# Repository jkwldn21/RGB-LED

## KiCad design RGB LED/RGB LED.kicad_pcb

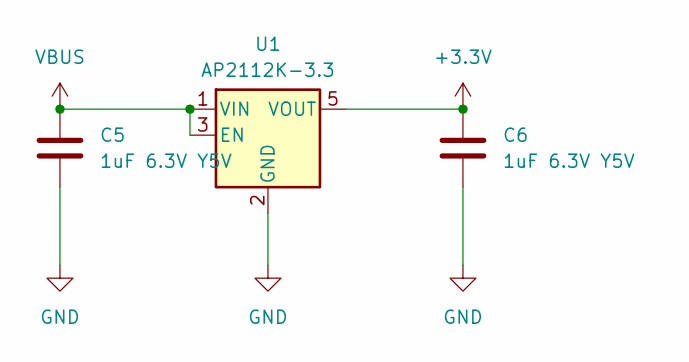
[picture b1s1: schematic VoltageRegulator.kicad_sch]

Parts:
C5, C6: 1uF 6.3V Y5V; C_0603_1608Metric
U1: AP2112K-3.3; SOT-23-5

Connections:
+3.3V: C6.1, U1.5 (VOUT); also elsewhere on the board
GND: C5.2, C6.2, U1.2 (GND); also elsewhere on the board
VBUS: C5.1, U1.1 (VIN), U1.3 (EN); also elsewhere on the board

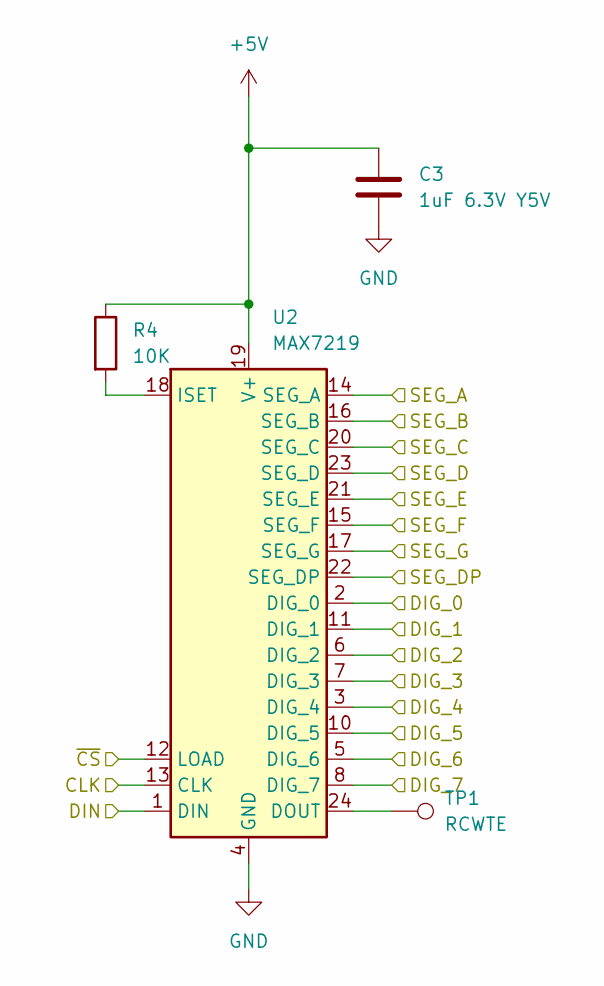
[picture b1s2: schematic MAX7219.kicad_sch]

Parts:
C3: 1uF 6.3V Y5V; C_0603_1608Metric
R4: 10K; R_0603_1608Metric
TP1: RCWTE; TestPoint_Keystone_5015_Micro-Minature
U2: MAX7219; SOP-24_7.5x15.4mm_P1.27mm

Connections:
+5V: C3.1, R4.1, U2.19 (V+)
/CLK: U2.13 (CLK); also elsewhere on the board
/DIN: U2.1 (DIN); also elsewhere on the board
/LED_Matrix/DIG_0: U2.2 (DIG_0); also elsewhere on the board
/LED_Matrix/DIG_1: U2.11 (DIG_1); also elsewhere on the board
/LED_Matrix/DIG_2: U2.6 (DIG_2); also elsewhere on the board
/LED_Matrix/DIG_3: U2.7 (DIG_3); also elsewhere on the board
/LED_Matrix/DIG_4: U2.3 (DIG_4); also elsewhere on the board
/LED_Matrix/DIG_5: U2.10 (DIG_5); also elsewhere on the board
/LED_Matrix/DIG_6: U2.5 (DIG_6); also elsewhere on the board
/LED_Matrix/DIG_7: U2.8 (DIG_7); also elsewhere on the board
/LED_Matrix/SEG_A: U2.14 (SEG_A); also elsewhere on the board
/LED_Matrix/SEG_B: U2.16 (SEG_B); also elsewhere on the board
/LED_Matrix/SEG_C: U2.20 (SEG_C); also elsewhere on the board
/LED_Matrix/SEG_D: U2.23 (SEG_D); also elsewhere on the board
/LED_Matrix/SEG_DP: U2.22 (SEG_DP); also elsewhere on the board
/LED_Matrix/SEG_E: U2.21 (SEG_E); also elsewhere on the board
/LED_Matrix/SEG_F: U2.15 (SEG_F); also elsewhere on the board
/LED_Matrix/SEG_G: U2.17 (SEG_G); also elsewhere on the board
/~CS: U2.12 (LOAD); also elsewhere on the board
GND: C3.2, U2.4 (GND), U2.9 (GND); also elsewhere on the board
unnamed: TP1.1, U2.24 (DOUT)
unnamed: R4.2, U2.18 (ISET)

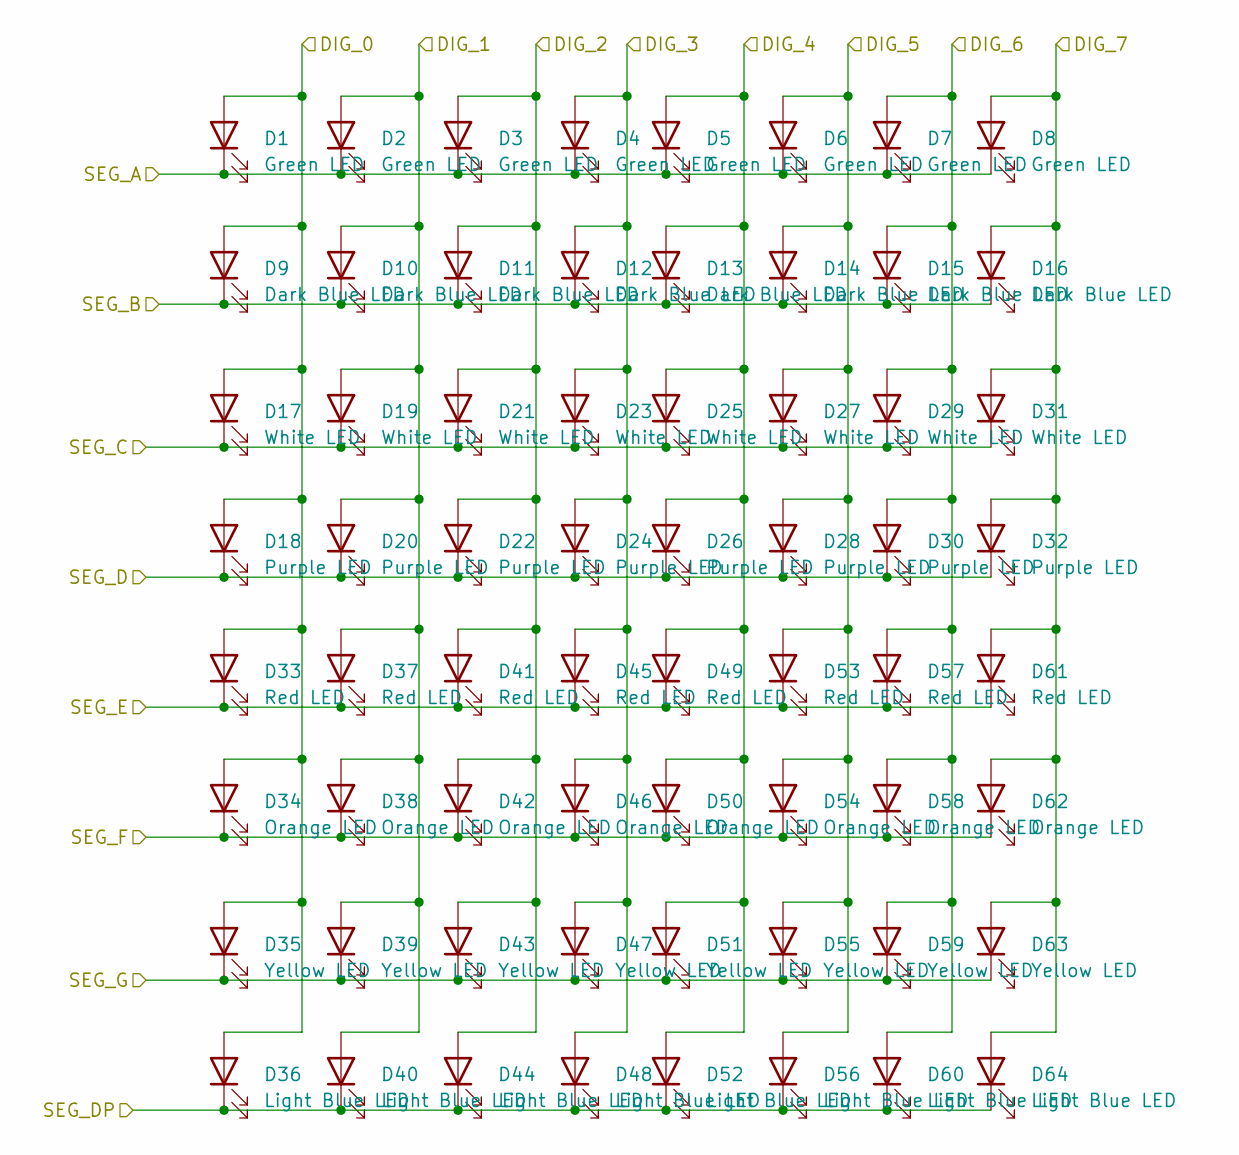
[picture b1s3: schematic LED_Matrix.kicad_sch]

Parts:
D1, D2, D3, D4, D5, D6, D7, D8: Green LED; LED_0603_1608Metric
D9, D10, D11, D12, D13, D14, D15, D16: Dark Blue LED; LED_0603_1608Metric
D17, D19, D21, D23, D25, D27, D29, D31: White LED; LED_0603_1608Metric
D18, D20, D22, D24, D26, D28, D30, D32: Purple LED; LED_0603_1608Metric
D33, D37, D41, D45, D49, D53, D57, D61: Red LED; LED_0603_1608Metric
D34, D38, D42, D46, D50, D54, D58, D62: Orange LED; LED_0603_1608Metric
D35, D39, D43, D47, D51, D55, D59, D63: Yellow LED; LED_0603_1608Metric
D36, D40, D44, D48, D52, D56, D60, D64: Light Blue LED; LED_0603_1608Metric

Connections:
/LED_Matrix/DIG_0: D1.2 (A), D9.2 (A), D17.2 (A), D18.2 (A), D33.2 (A), D34.2 (A), D35.2 (A), D36.2 (A); also elsewhere on the board
/LED_Matrix/DIG_1: D2.2 (A), D10.2 (A), D19.2 (A), D20.2 (A), D37.2 (A), D38.2 (A), D39.2 (A), D40.2 (A); also elsewhere on the board
/LED_Matrix/DIG_2: D3.2 (A), D11.2 (A), D21.2 (A), D22.2 (A), D41.2 (A), D42.2 (A), D43.2 (A), D44.2 (A); also elsewhere on the board
/LED_Matrix/DIG_3: D4.2 (A), D12.2 (A), D23.2 (A), D24.2 (A), D45.2 (A), D46.2 (A), D47.2 (A), D48.2 (A); also elsewhere on the board
/LED_Matrix/DIG_4: D5.2 (A), D13.2 (A), D25.2 (A), D26.2 (A), D49.2 (A), D50.2 (A), D51.2 (A), D52.2 (A); also elsewhere on the board
/LED_Matrix/DIG_5: D6.2 (A), D14.2 (A), D27.2 (A), D28.2 (A), D53.2 (A), D54.2 (A), D55.2 (A), D56.2 (A); also elsewhere on the board
/LED_Matrix/DIG_6: D7.2 (A), D15.2 (A), D29.2 (A), D30.2 (A), D57.2 (A), D58.2 (A), D59.2 (A), D60.2 (A); also elsewhere on the board
/LED_Matrix/DIG_7: D8.2 (A), D16.2 (A), D31.2 (A), D32.2 (A), D61.2 (A), D62.2 (A), D63.2 (A), D64.2 (A); also elsewhere on the board
/LED_Matrix/SEG_A: D1.1 (K), D2.1 (K), D3.1 (K), D4.1 (K), D5.1 (K), D6.1 (K), D7.1 (K), D8.1 (K); also elsewhere on the board
/LED_Matrix/SEG_B: D9.1 (K), D10.1 (K), D11.1 (K), D12.1 (K), D13.1 (K), D14.1 (K), D15.1 (K), D16.1 (K); also elsewhere on the board
/LED_Matrix/SEG_C: D17.1 (K), D19.1 (K), D21.1 (K), D23.1 (K), D25.1 (K), D27.1 (K), D29.1 (K), D31.1 (K); also elsewhere on the board
/LED_Matrix/SEG_D: D18.1 (K), D20.1 (K), D22.1 (K), D24.1 (K), D26.1 (K), D28.1 (K), D30.1 (K), D32.1 (K); also elsewhere on the board
/LED_Matrix/SEG_DP: D36.1 (K), D40.1 (K), D44.1 (K), D48.1 (K), D52.1 (K), D56.1 (K), D60.1 (K), D64.1 (K); also elsewhere on the board
/LED_Matrix/SEG_E: D33.1 (K), D37.1 (K), D41.1 (K), D45.1 (K), D49.1 (K), D53.1 (K), D57.1 (K), D61.1 (K); also elsewhere on the board
/LED_Matrix/SEG_F: D34.1 (K), D38.1 (K), D42.1 (K), D46.1 (K), D50.1 (K), D54.1 (K), D58.1 (K), D62.1 (K); also elsewhere on the board
/LED_Matrix/SEG_G: D35.1 (K), D39.1 (K), D43.1 (K), D47.1 (K), D51.1 (K), D55.1 (K), D59.1 (K), D63.1 (K); also elsewhere on the board

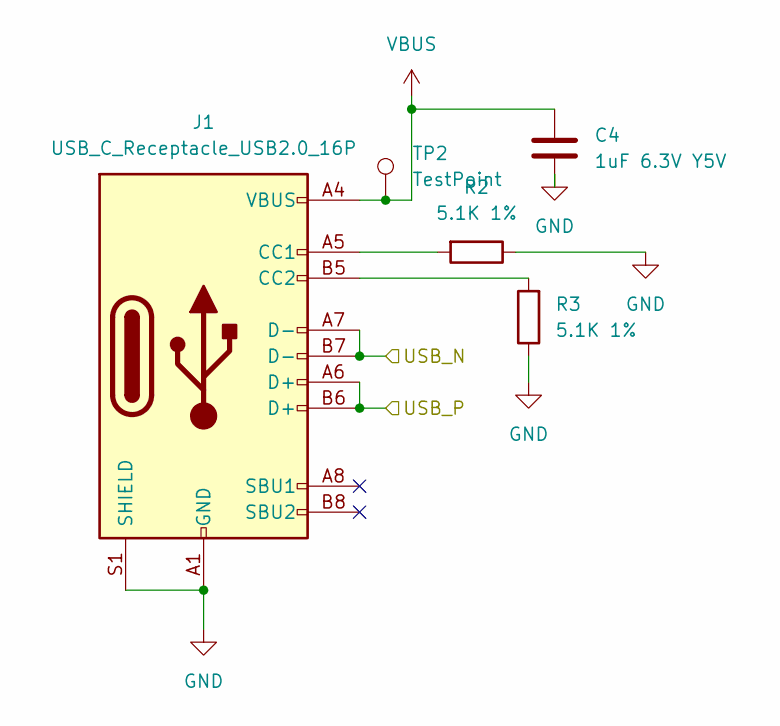
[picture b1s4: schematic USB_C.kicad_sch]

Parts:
C4: 1uF 6.3V Y5V; C_0603_1608Metric
J1: USB_C_Receptacle_USB2.0_16P; USB_C_Receptacle_GCT_USB4085
R2, R3: 5.1K 1%; R_0603_1608Metric
TP2: TestPoint; TestPoint_Keystone_5015_Micro-Minature

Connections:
/USB_N: J1.A7 (D-), J1.B7 (D-); also elsewhere on the board
/USB_P: J1.A6 (D+), J1.B6 (D+); also elsewhere on the board
GND: C4.2, J1.A1 (GND), J1.A12 (GND), J1.B1 (GND), J1.B12 (GND), J1.S1 (SHIELD), R2.1, R3.1; also elsewhere on the board
unnamed: J1.A5 (CC1), R2.2
unnamed: J1.B5 (CC2), R3.2
VBUS: C4.1, J1.A4 (VBUS), J1.A9 (VBUS), J1.B4 (VBUS), J1.B9 (VBUS), TP2.1; also elsewhere on the board

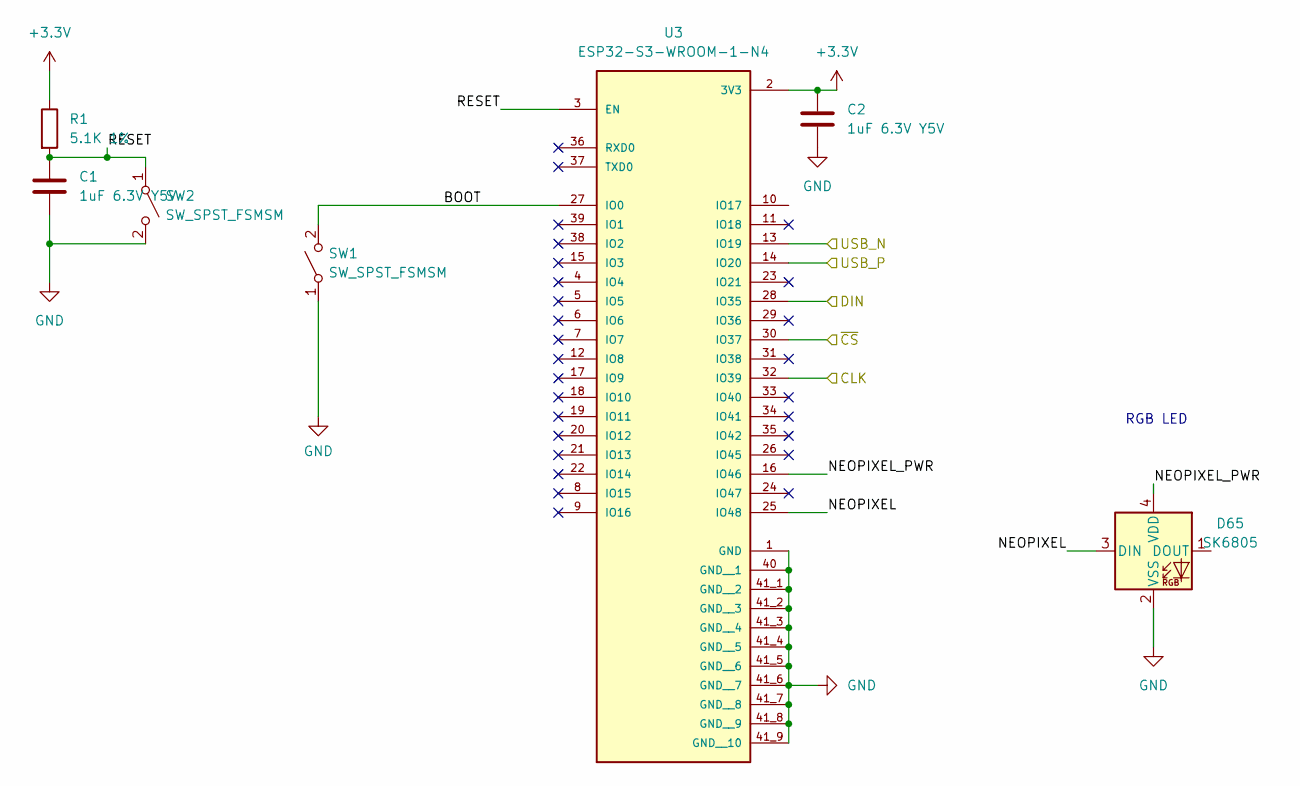
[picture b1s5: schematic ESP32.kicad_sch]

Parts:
C1, C2: 1uF 6.3V Y5V; C_0603_1608Metric
D65: SK6805; LED_SK6805_PLCC4_2.4x2.7mm_P1.3mm
R1: 5.1K 1%; R_0603_1608Metric
SW1, SW2: SW_SPST_FSMSM
U3: ESP32-S3-WROOM-1-N4; XCVR_ESP32-S3-WROOM-1-N4; PARTREV v1.0

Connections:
+3.3V: C2.1, R1.1, U3.2 (3V3); also elsewhere on the board
/CLK: U3.32 (IO39); also elsewhere on the board
/DIN: U3.28 (IO35); also elsewhere on the board
/ESP32/BOOT: SW1.2 (B), U3.27 (IO0)
/ESP32/NEOPIXEL: D65.3 (DIN), U3.25 (IO48)
/ESP32/NEOPIXEL_PWR: D65.4 (VDD), U3.16 (IO46)
/ESP32/RESET: C1.1, R1.2, SW2.1 (A), U3.3 (EN)
/USB_N: U3.13 (IO19); also elsewhere on the board
/USB_P: U3.14 (IO20); also elsewhere on the board
/~CS: U3.30 (IO37); also elsewhere on the board
GND: C1.2, C2.2, D65.2 (VSS), SW1.1 (A), SW2.2 (B), U3.1 (GND), U3.40 (GND__1), U3.41_1 (GND__2), U3.41_2 (GND__3), U3.41_3 (GND__4), U3.41_4 (GND__5), U3.41_5 (GND__6), U3.41_6 (GND__7), U3.41_7 (GND__8), U3.41_8 (GND__9), U3.41_9 (GND__10), U3.41_10, U3.41_11, U3.41_12, U3.41_13, U3.41_14, U3.41_15, U3.41_16, U3.41_17, U3.41_18, U3.41_19, U3.41_20, U3.41_21; also elsewhere on the board

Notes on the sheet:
RGB LED

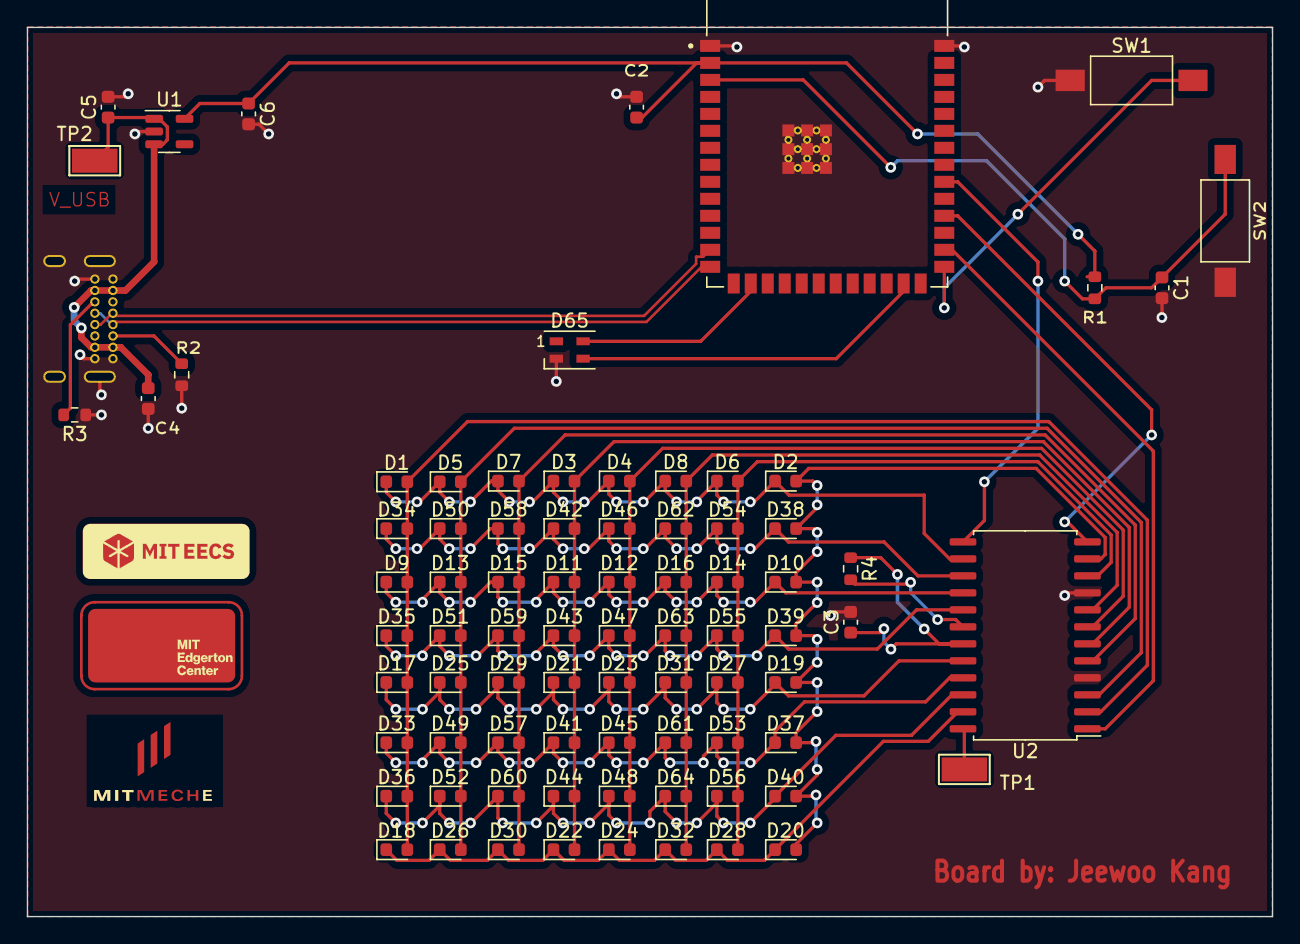
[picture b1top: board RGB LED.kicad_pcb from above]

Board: 2 copper layers, 93.1 x 66.5 mm, 83 parts (1 on the bottom side), 33 nets.

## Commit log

2024-01-11 edited according to feedback
2024-01-12 added footprints
2024-01-16 started layout
2024-01-16 schematic edits
2024-01-16 layout update
2024-01-17 changed layout, added traces/vias
2024-01-17 draft of layout
2024-01-18 edited layout according to feedback
2024-01-19 added logos
2024-01-19 added meche logo
2024-01-19 ran drc and edited according to drc
2024-01-21 changed vias to gnd
2024-01-21 added name
